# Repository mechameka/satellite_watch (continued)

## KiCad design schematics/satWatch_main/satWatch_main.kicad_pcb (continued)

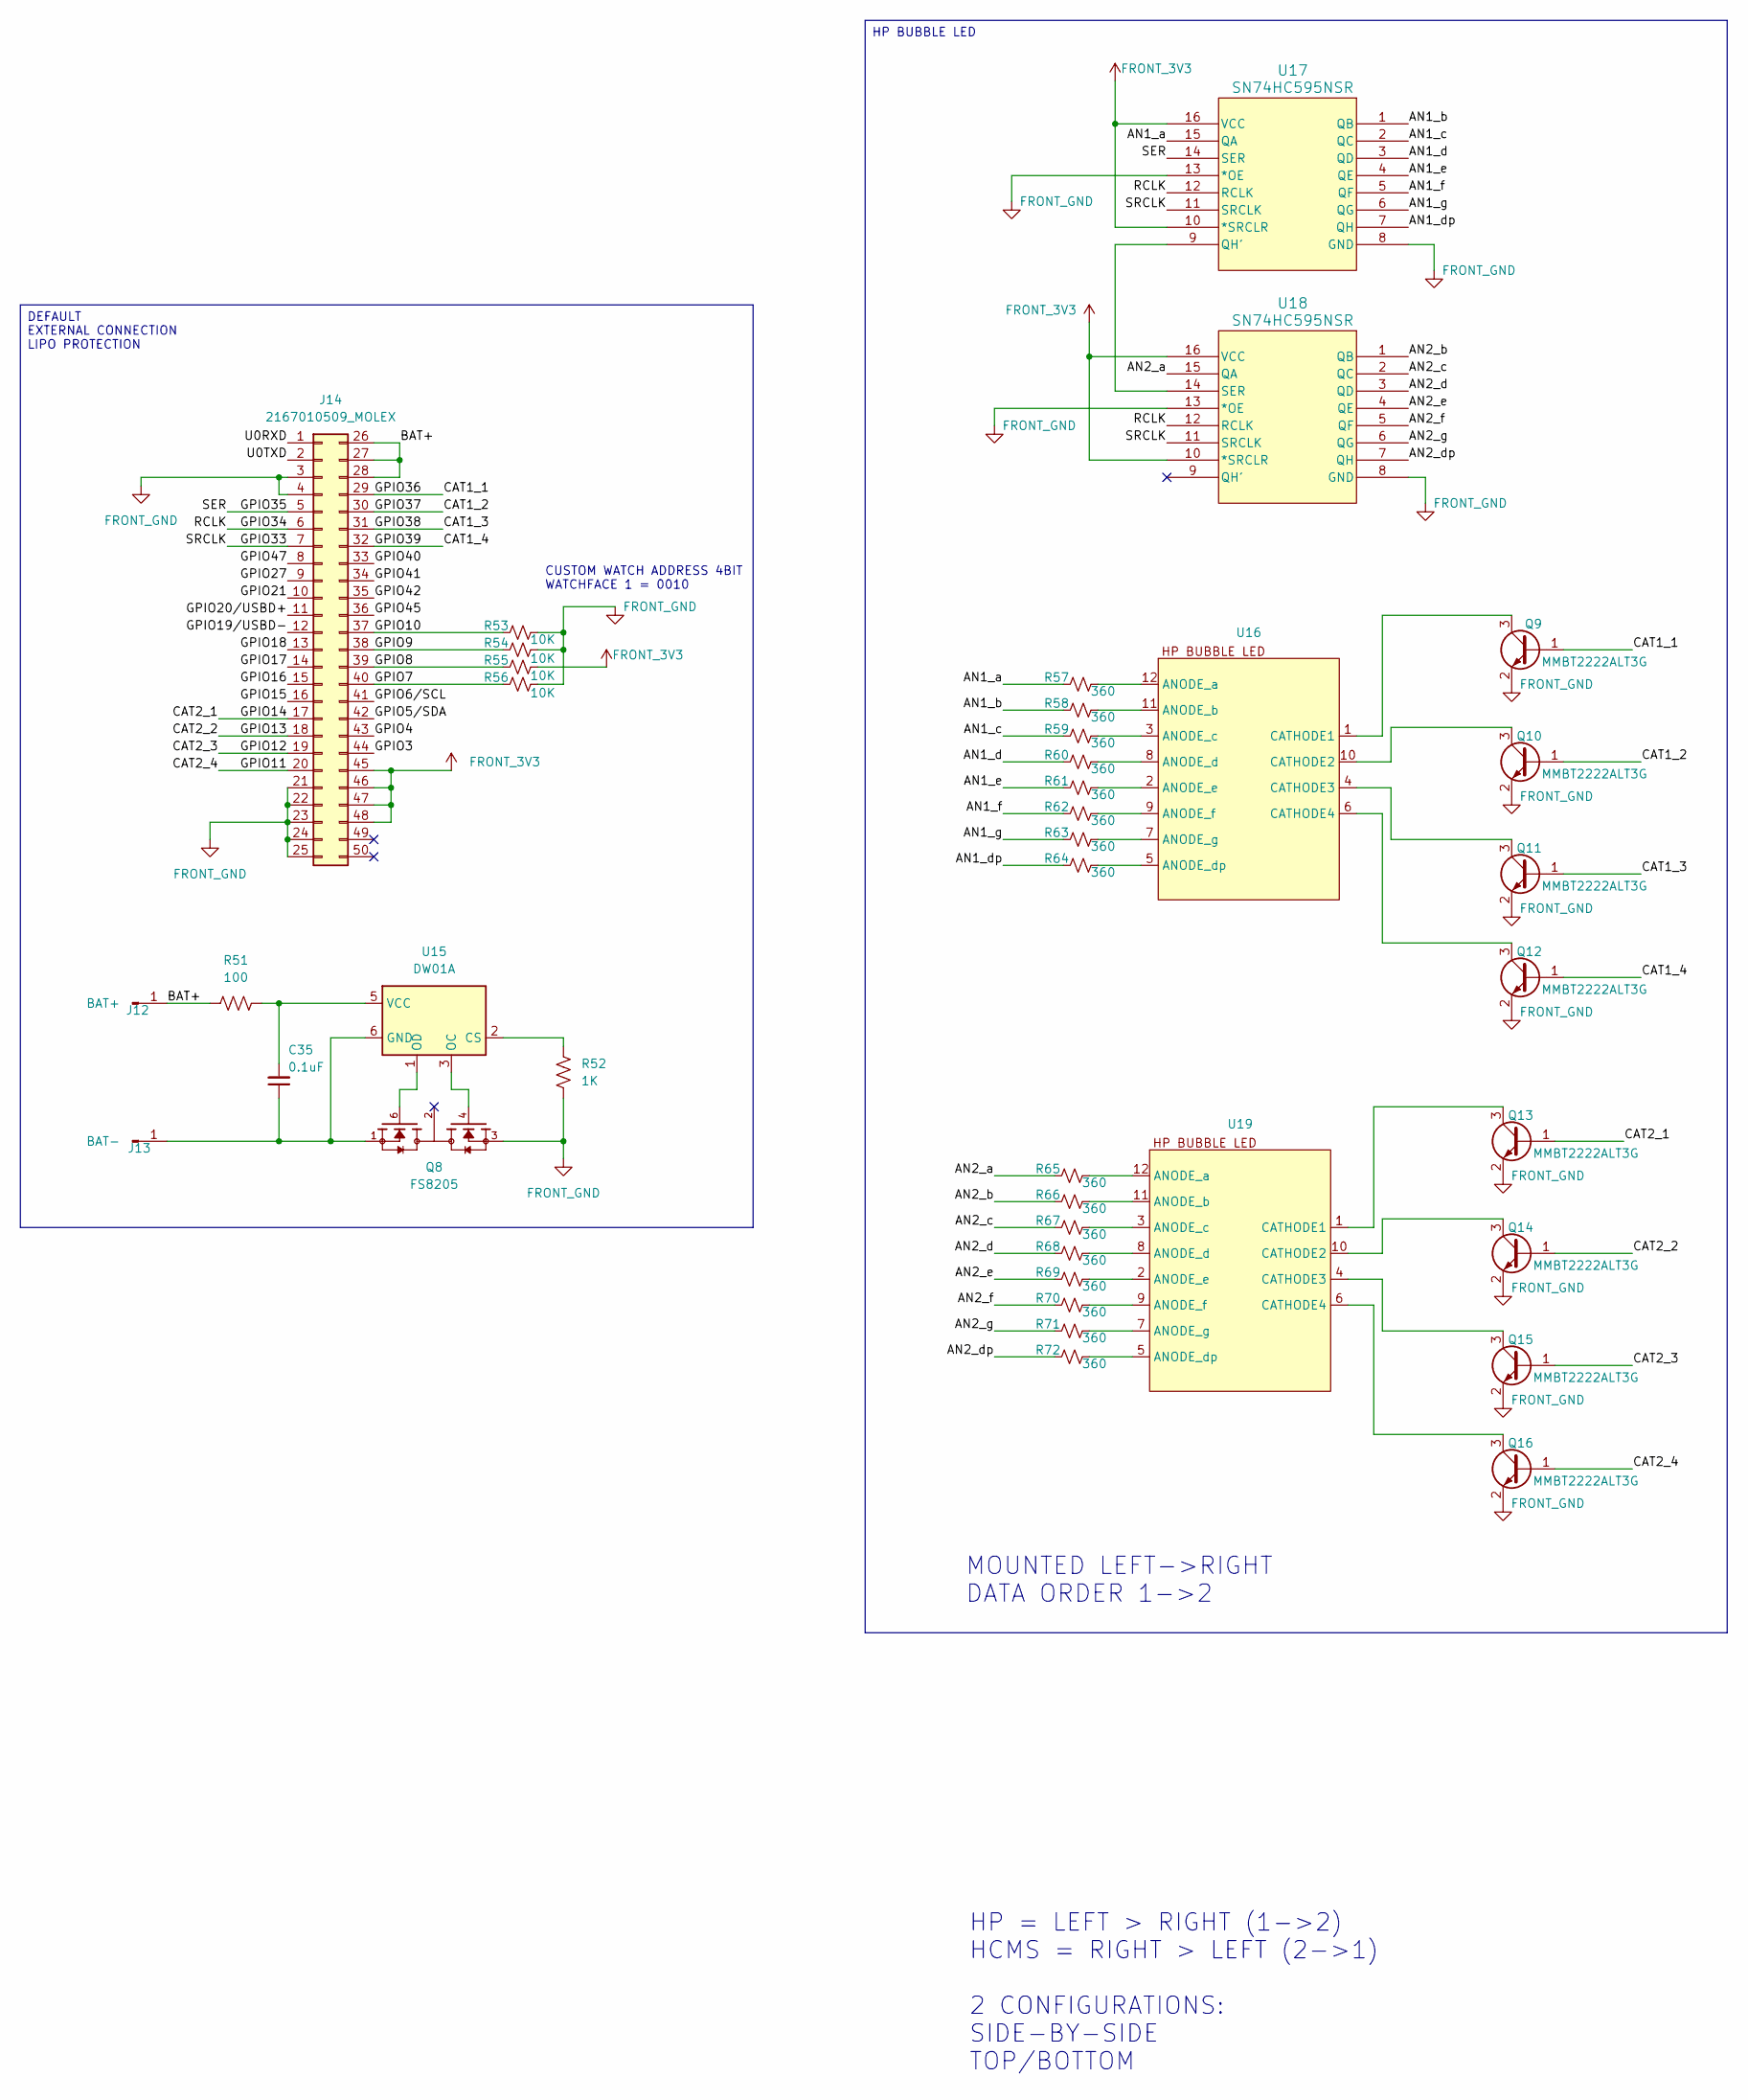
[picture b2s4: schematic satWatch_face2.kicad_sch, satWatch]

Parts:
C35: 0.1uF; C_0402_1005Metric_Pad0.74x0.62mm_HandSolder
J12: BAT+; SolderWirePad_1x01_SMD_3x6mm
J13: BAT-; SolderWirePad_1x01_SMD_3x6mm
J14: 2167010509_MOLEX; CON_2167010509_MOL
Q8: FS8205; SOT95P280X145-6N; PARTREV 1.9
Q9, Q10, Q11, Q12, Q13, Q14, Q15, Q16: MMBT2222ALT3G; SOT-23
R51: 100; R_0402_1005Metric_Pad0.72x0.64mm_HandSolder
R52: 1K; R_0402_1005Metric_Pad0.72x0.64mm_HandSolder
R53, R54, R55, R56: 10K; R_0402_1005Metric_Pad0.72x0.64mm_HandSolder
R57, R58, R59, R60, R61, R62, R63, R64, R65, R66, R67, R68, R69, R70, R71, R72: 360; R_0402_1005Metric_Pad0.72x0.64mm_HandSolder
U15: DW01A; SOT-23-6
U16, U19: DIP-12_W7.62mm
U17, U18: SN74HC595NSR; NS16-L

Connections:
/face2/AN1_a: R57.1, U17.15 (QA)
/face2/AN1_b: R58.1, U17.1 (QB)
/face2/AN1_c: R59.1, U17.2 (QC)
/face2/AN1_d: R60.1, U17.3 (QD)
/face2/AN1_dp: R64.1, U17.7 (QH)
/face2/AN1_e: R61.1, U17.4 (QE)
/face2/AN1_f: R62.1, U17.5 (QF)
/face2/AN1_g: R63.1, U17.6 (QG)
/face2/AN2_a: R65.1, U18.15 (QA)
/face2/AN2_b: R66.1, U18.1 (QB)
/face2/AN2_c: R67.1, U18.2 (QC)
/face2/AN2_d: R68.1, U18.3 (QD)
/face2/AN2_dp: R72.1, U18.7 (QH)
/face2/AN2_e: R69.1, U18.4 (QE)
/face2/AN2_f: R70.1, U18.5 (QF)
/face2/AN2_g: R71.1, U18.6 (QG)
/face2/BAT+: J12.1 (Pin_1_1), J14.26, J14.27, J14.28, R51.1
/face2/CAT1_1: J14.29, Q9.1 (B)
/face2/CAT1_2: J14.30, Q10.1 (B)
/face2/CAT1_3: J14.31, Q11.1 (B)
/face2/CAT1_4: J14.32, Q12.1 (B)
/face2/CAT2_1: J14.17, Q13.1 (B)
/face2/CAT2_2: J14.18, Q14.1 (B)
/face2/CAT2_3: J14.19, Q15.1 (B)
/face2/CAT2_4: J14.20, Q16.1 (B)
/face2/GPIO3: J14.44
/face2/GPIO4: J14.43
/face2/GPIO5/SDA: J14.42
/face2/GPIO6/SCL: J14.41
/face2/GPIO7: J14.40, R56.1
/face2/GPIO8: J14.39, R55.1
/face2/GPIO9: J14.38, R54.1
/face2/GPIO10: J14.37, R53.1
/face2/GPIO15: J14.16
/face2/GPIO16: J14.15
/face2/GPIO17: J14.14
/face2/GPIO18: J14.13
/face2/GPIO19/USBD-: J14.12
/face2/GPIO20/USBD+: J14.11
/face2/GPIO21: J14.10
/face2/GPIO27: J14.9
/face2/GPIO33: J14.7, U17.11 (SRCLK), U18.11 (SRCLK)
/face2/GPIO34: J14.6, U17.12 (RCLK), U18.12 (RCLK)
/face2/GPIO35: J14.5, U17.14 (SER)
/face2/GPIO40: J14.33
/face2/GPIO41: J14.34
/face2/GPIO42: J14.35
/face2/GPIO45: J14.36
/face2/GPIO47: J14.8
/face2/U0RXD: J14.1
/face2/U0TXD: J14.2
FRONT_3V3: J14.45, J14.46, J14.47, J14.48, R55.2, U17.10 (*SRCLR), U17.16 (VCC), U18.10 (*SRCLR), U18.16 (VCC); also elsewhere on the board
FRONT_GND: J14.3, J14.4, J14.21, J14.22, J14.23, J14.24, J14.25, Q8.3, Q9.2 (E), Q10.2 (E), Q11.2 (E), Q12.2 (E), Q13.2 (E), Q14.2 (E), Q15.2 (E), Q16.2 (E), R52.1, R53.2, R54.2, R56.2, U17.8 (GND), U17.13 (*OE), U18.8 (GND), U18.13 (*OE); also elsewhere on the board
unnamed: C35.1, J13.1 (Pin_1_1), Q8.1, U15.6 (GND)
unnamed: Q9.3 (C), U16.1 (CATHODE1)
unnamed: Q10.3 (C), U16.10 (CATHODE2)
unnamed: Q11.3 (C), U16.4 (CATHODE3)
unnamed: Q12.3 (C), U16.6 (CATHODE4)
unnamed: Q13.3 (C), U19.1 (CATHODE1)
unnamed: Q14.3 (C), U19.10 (CATHODE2)
unnamed: Q15.3 (C), U19.4 (CATHODE3)
unnamed: Q16.3 (C), U19.6 (CATHODE4)
unnamed: R52.2, U15.2 (CS)
unnamed: Q8.4, U15.3 (OC)
unnamed: Q8.6, U15.1 (OD)
unnamed: C35.2, R51.2, U15.5 (VCC)
unnamed: R57.2, U16.12 (ANODE_a)
unnamed: R58.2, U16.11 (ANODE_b)
unnamed: R59.2, U16.3 (ANODE_c)
unnamed: R60.2, U16.8 (ANODE_d)
unnamed: R64.2, U16.5 (ANODE_dp)
unnamed: R61.2, U16.2 (ANODE_e)
unnamed: R62.2, U16.9 (ANODE_f)
unnamed: R63.2, U16.7 (ANODE_g)
unnamed: U17.9 (QH'), U18.14 (SER)
unnamed: R65.2, U19.12 (ANODE_a)
unnamed: R66.2, U19.11 (ANODE_b)
unnamed: R67.2, U19.3 (ANODE_c)
unnamed: R68.2, U19.8 (ANODE_d)
unnamed: R72.2, U19.5 (ANODE_dp)
unnamed: R69.2, U19.2 (ANODE_e)
unnamed: R70.2, U19.9 (ANODE_f)
unnamed: R71.2, U19.7 (ANODE_g)

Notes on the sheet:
MOUNTED LEFT->RIGHT DATA ORDER 1->2
CUSTOM WATCH ADDRESS 4BIT WATCHFACE 1 = 0010
HP = LEFT > RIGHT (1->2) HCMS = RIGHT > LEFT (2->1) 2 CONFIGURATIONS: SIDE-BY-SIDE TOP/BOTTOM
DEFAULT EXTERNAL CONNECTION LIPO PROTECTION
HP BUBBLE LED

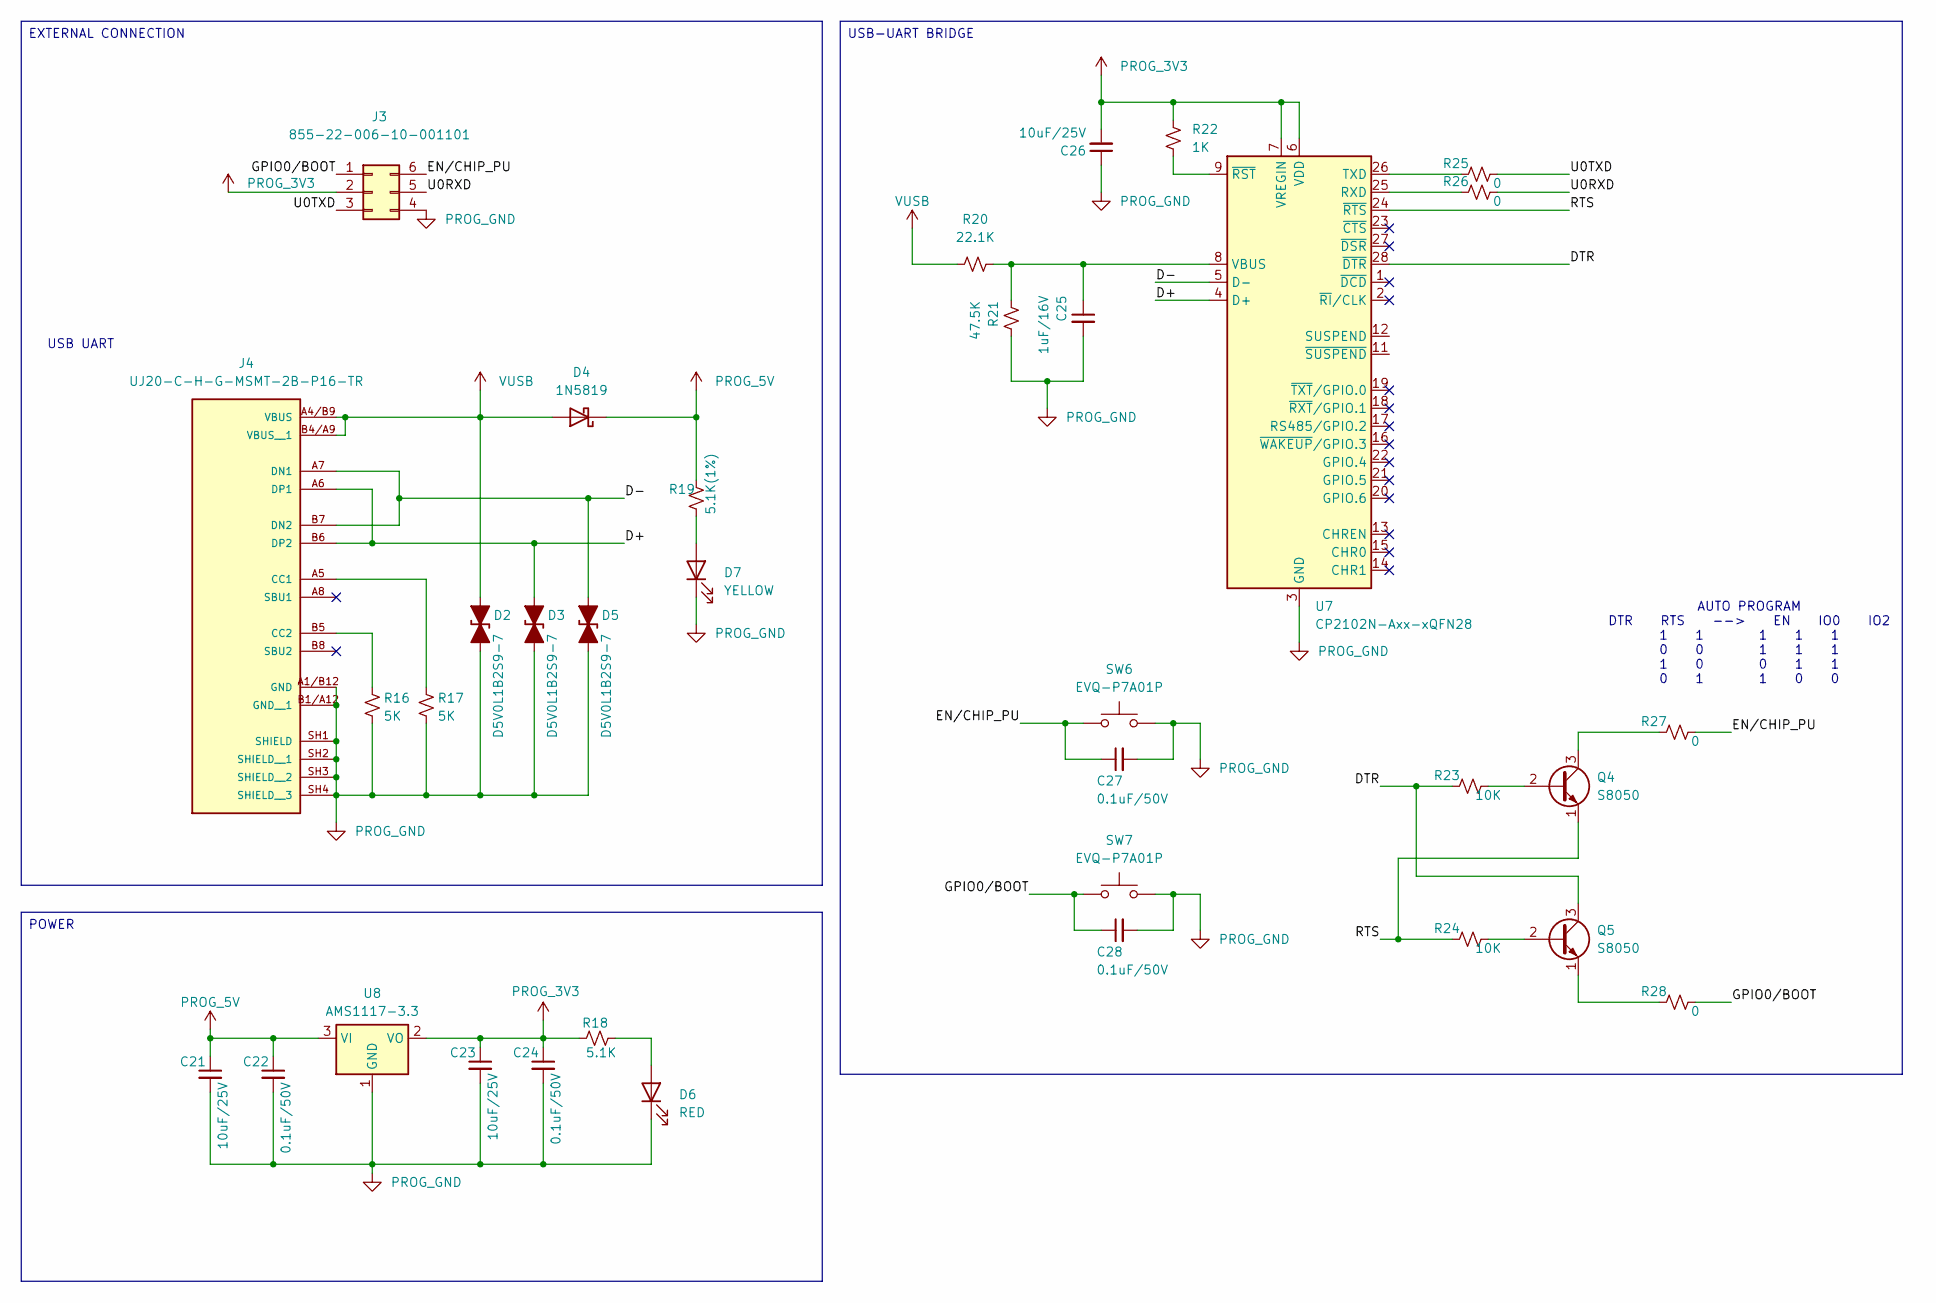
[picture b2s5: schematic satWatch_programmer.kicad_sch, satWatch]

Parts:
C21, C23, C26: 10uF/25V; C_0603_1608Metric_Pad1.08x0.95mm_HandSolder
C22, C24, C27, C28: 0.1uF/50V; C_0603_1608Metric_Pad1.08x0.95mm_HandSolder
C25: 1uF/16V; C_0603_1608Metric_Pad1.08x0.95mm_HandSolder
D2, D3, D5: D5V0L1B2S9-7; D_SOD-923
D4: 1N5819; D_SOD-123
D6: RED; LED_0603_1608Metric_Pad1.05x0.95mm_HandSolder
D7: YELLOW; LED_0603_1608Metric_Pad1.05x0.95mm_HandSolder
J3: 855-22-006-10-001101; 8552200610001101
J4: UJ20-C-H-G-MSMT-2B-P16-TR; SAMESKY_UJ20-C-H-G-MSMT-2B-P16-TR; PARTREV 1.0
Q4, Q5: S8050; SOT-23_Handsoldering
R16, R17: 5K; R_0603_1608Metric_Pad0.98x0.95mm_HandSolder
R18: 5.1K; R_0603_1608Metric_Pad0.98x0.95mm_HandSolder
R19: 5.1K(1%); R_0603_1608Metric_Pad0.98x0.95mm_HandSolder
R20: 22.1K; R_0603_1608Metric_Pad0.98x0.95mm_HandSolder
R21: 47.5K; R_0603_1608Metric_Pad0.98x0.95mm_HandSolder
R22: 1K; R_0603_1608Metric_Pad0.98x0.95mm_HandSolder
R23, R24: 10K; R_0603_1608Metric_Pad0.98x0.95mm_HandSolder
R25, R26, R27, R28: 0; R_0603_1608Metric_Pad0.98x0.95mm_HandSolder
SW6, SW7: EVQ-P7A01P; SW_SPST_EVQP7A
U7: CP2102N-Axx-xQFN28; QFN-28-1EP_5x5mm_P0.5mm_EP3.35x3.35mm
U8: AMS1117-3.3; SOT-223-3_TabPin2

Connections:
/Programmer/D+: D3.1 (A1), J4.A6 (DP1), J4.B6 (DP2), U7.4 (D+)
/Programmer/D-: D5.1 (A1), J4.A7 (DN1), J4.B7 (DN2), U7.5 (D-)
/Programmer/DTR: Q5.3 (C), R23.2, U7.28 (~DTR)
/Programmer/EN/CHIP_PU: C27.1, J3.6, R27.1, SW6.1
/Programmer/GPIO0/BOOT: C28.1, J3.1, R28.1, SW7.1
/Programmer/RTS: Q4.1 (E), R24.2, U7.24 (~RTS)
/Programmer/U0RXD: J3.5, R26.1
/Programmer/U0TXD: J3.3, R25.1
unnamed: D6.2 (A), R18.2
unnamed: D7.2 (A), R19.1
unnamed: J4.A5 (CC1), R17.1
unnamed: J4.B5 (CC2), R16.1
unnamed: Q4.2 (B), R23.1
unnamed: Q4.3 (C), R27.2
unnamed: Q5.2 (B), R24.1
unnamed: Q5.1 (E), R28.2
unnamed: R26.2, U7.25 (RXD)
unnamed: R25.2, U7.26 (TXD)
unnamed: C25.1, R20.2, R21.1, U7.8 (VBUS)
unnamed: R22.1, U7.9 (~RST)
PROG_3V3: C23.1, C24.1, C26.2, J3.2, R18.1, R22.2, U7.6 (VDD), U7.7 (VREGIN), U8.2 (VO)
PROG_5V: C21.1, C22.1, D4.1 (K), R19.2, U8.3 (VI)
PROG_GND: C21.2, C22.2, C23.2, C24.2, C25.2, C26.1, C27.2, C28.2, D2.2 (A2), D3.2 (A2), D5.2 (A2), D6.1 (K), D7.1 (K), J3.4, J4.A1/B12 (GND), J4.B1/A12 (GND__1), J4.SH1 (SHIELD), J4.SH2 (SHIELD__1), J4.SH3 (SHIELD__2), J4.SH4 (SHIELD__3), R16.2, R17.2, R21.2, SW6.2, SW7.2, U7.3 (GND), U7.29 (GND), U8.1 (GND)
VUSB: D2.1 (A1), D4.2 (A), J4.A4/B9 (VBUS), J4.B4/A9 (VBUS__1), R20.1

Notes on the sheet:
USB UART
AUTO PROGRAM DTR RTS --> EN IO0 IO2 1 1 1 1 1 0 0 1 1 1 1 0 0 1 1 0 1 1 0 0
USB-UART BRIDGE
EXTERNAL CONNECTION
POWER

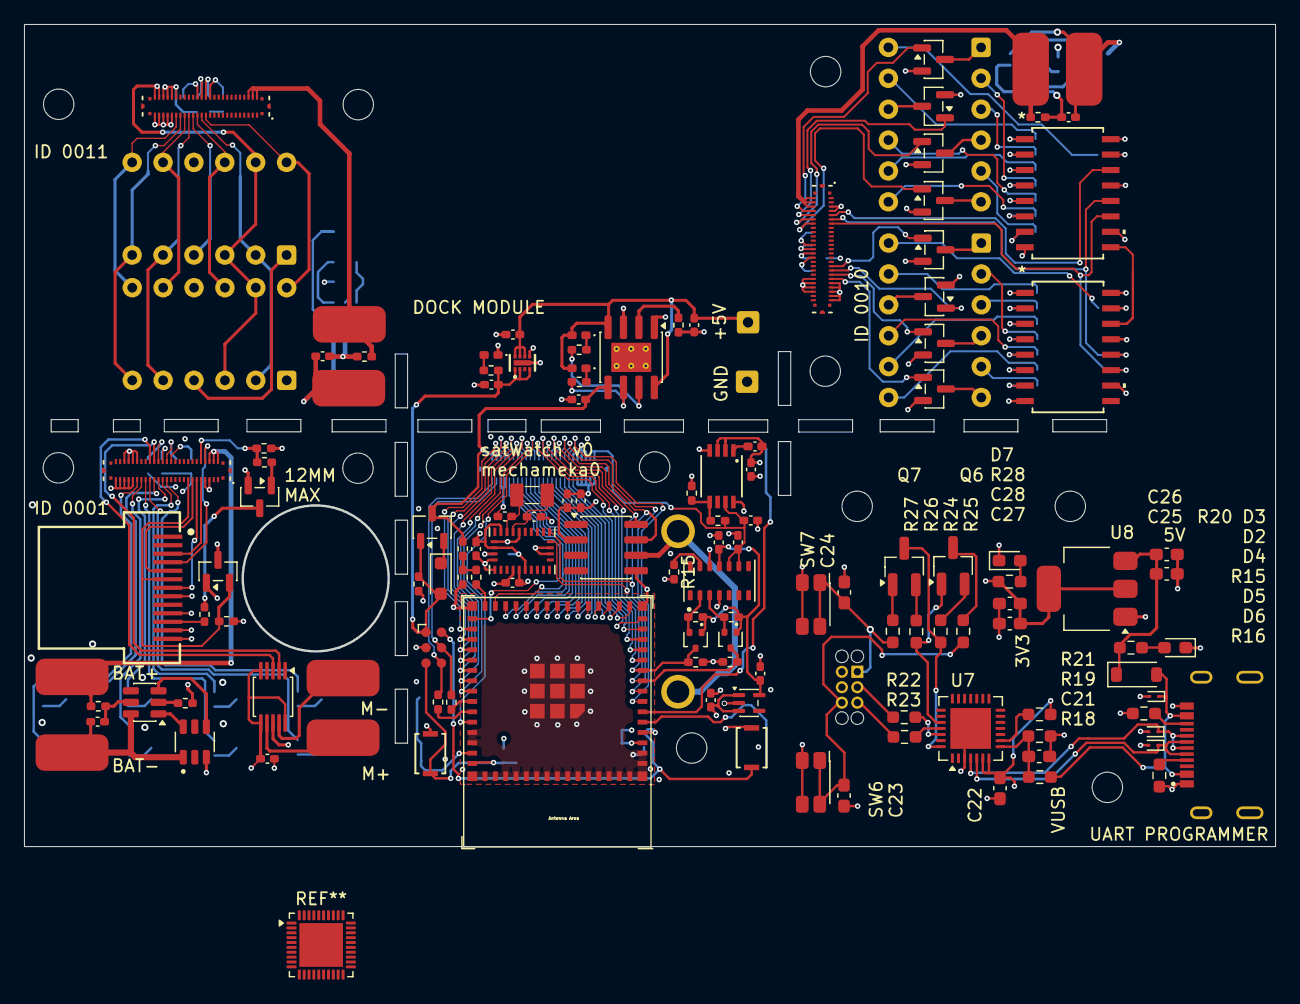
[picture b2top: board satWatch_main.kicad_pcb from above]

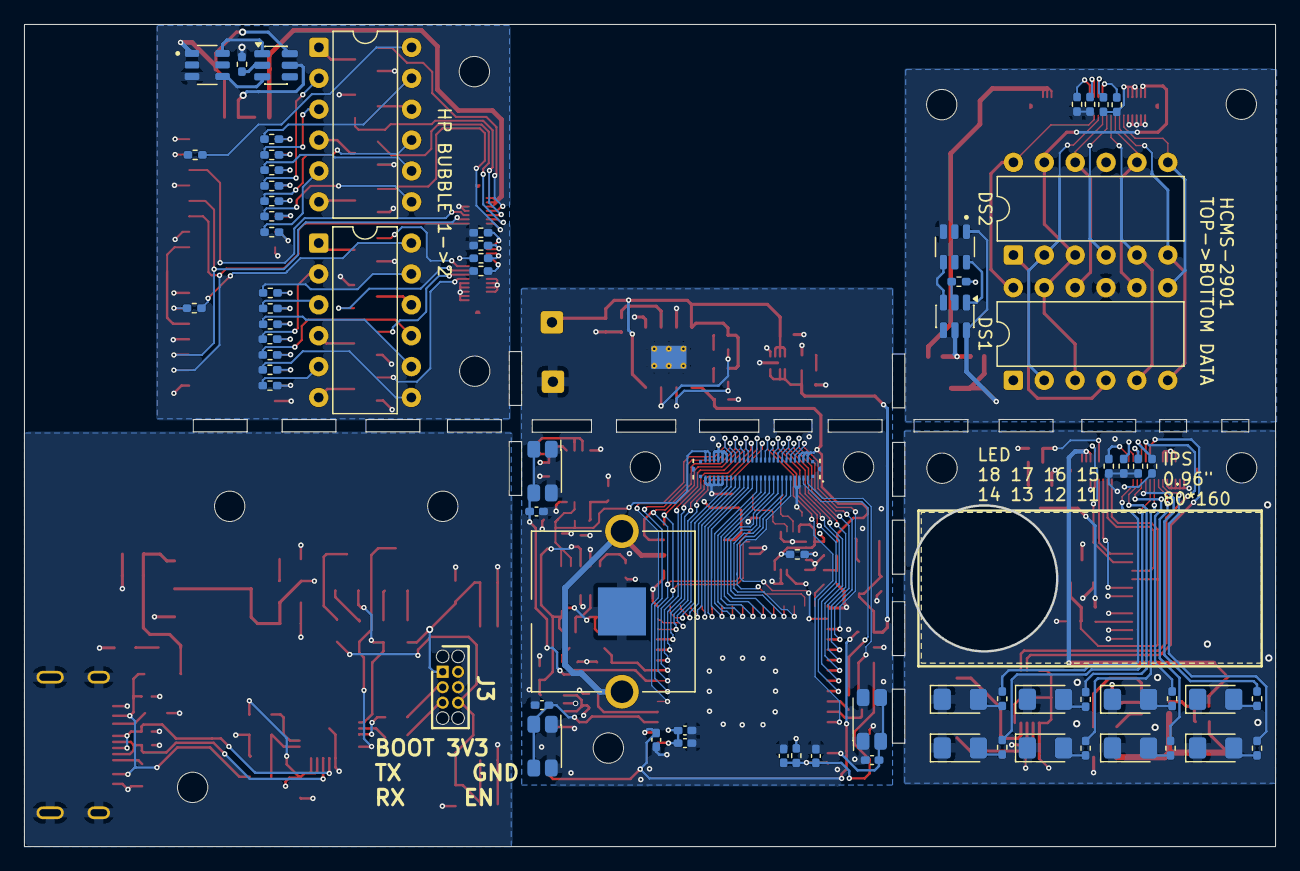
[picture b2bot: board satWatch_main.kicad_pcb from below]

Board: 4 copper layers, 102.9 x 67.6 mm, 210 parts (70 on the bottom side), 213 nets.

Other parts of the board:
H1, H1#2, H1#3, H1#4, H1#5, H2, H2#2, H2#3, H2#4, H2#5, H3, H3#2: MountingHole; MountingHole_2.5mm

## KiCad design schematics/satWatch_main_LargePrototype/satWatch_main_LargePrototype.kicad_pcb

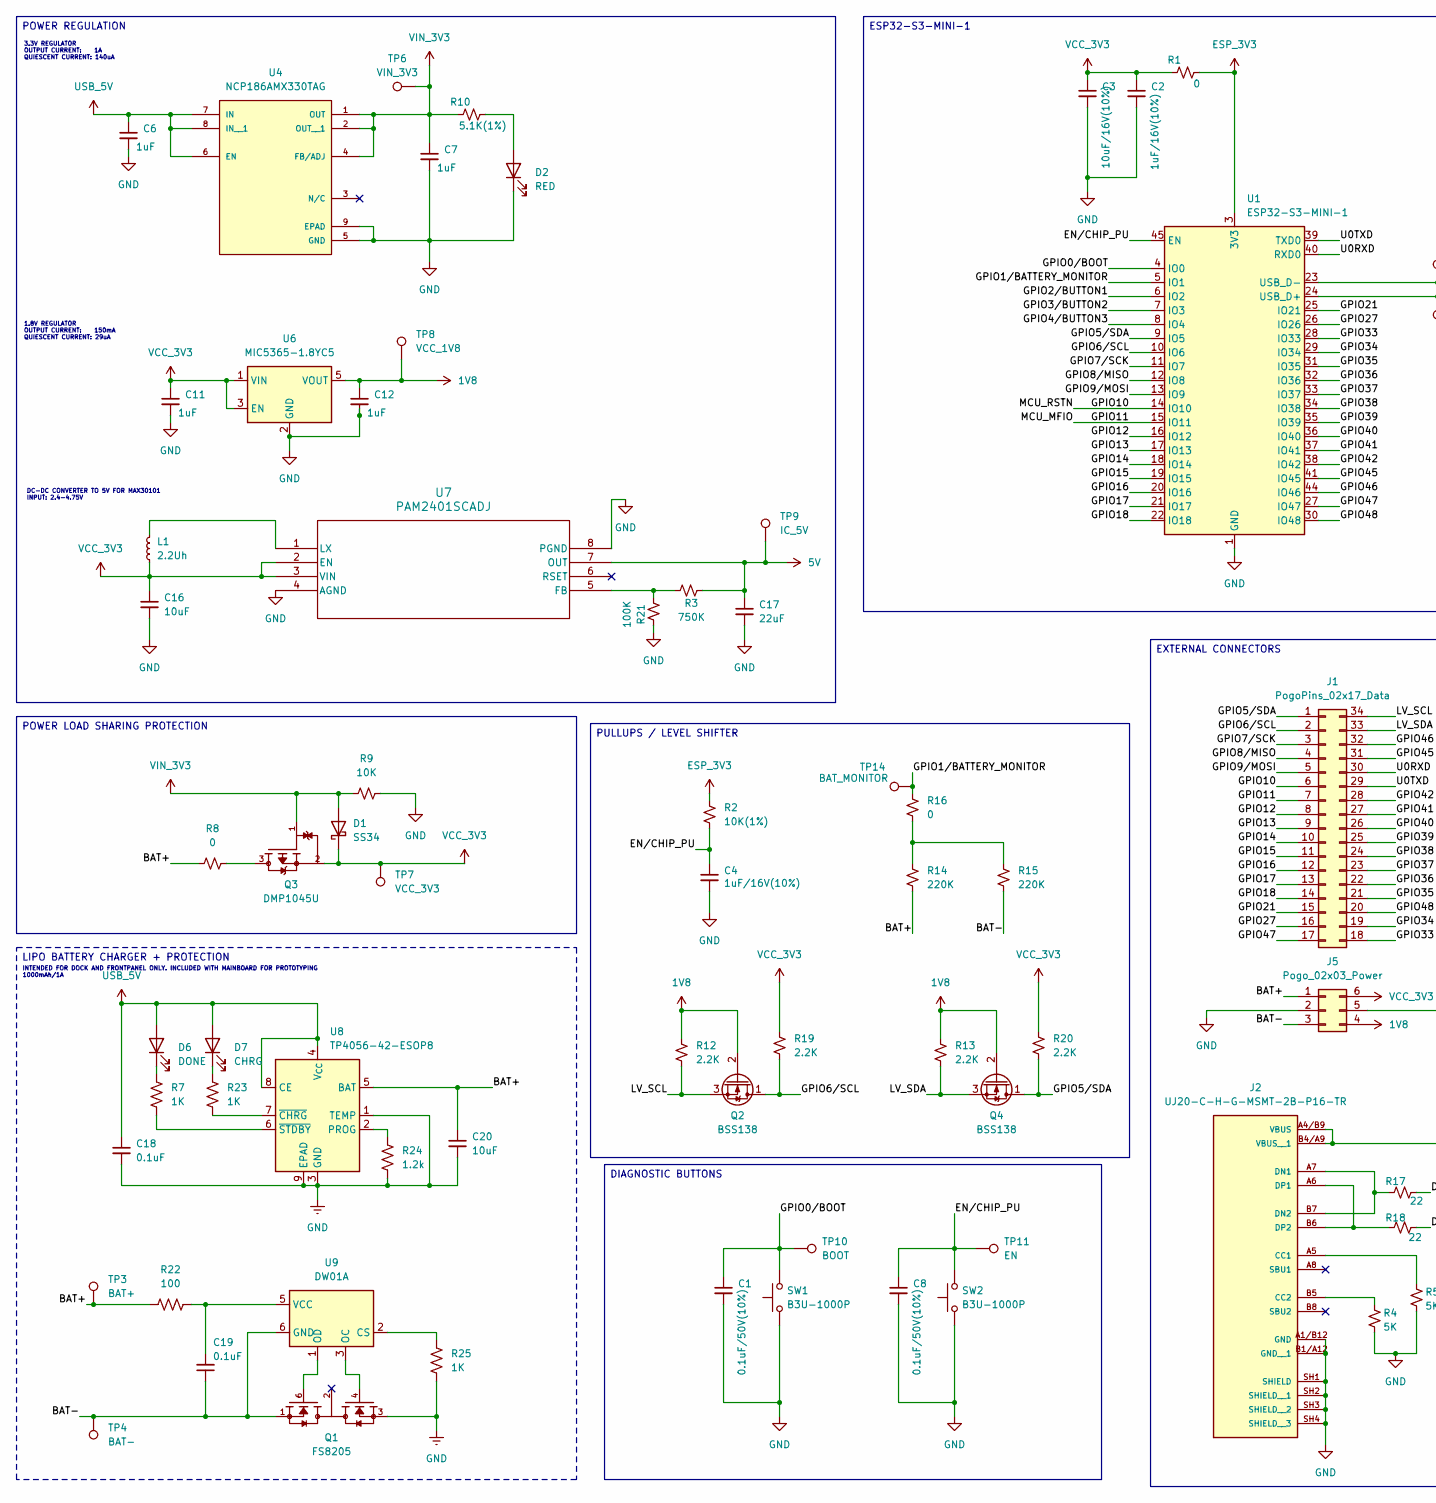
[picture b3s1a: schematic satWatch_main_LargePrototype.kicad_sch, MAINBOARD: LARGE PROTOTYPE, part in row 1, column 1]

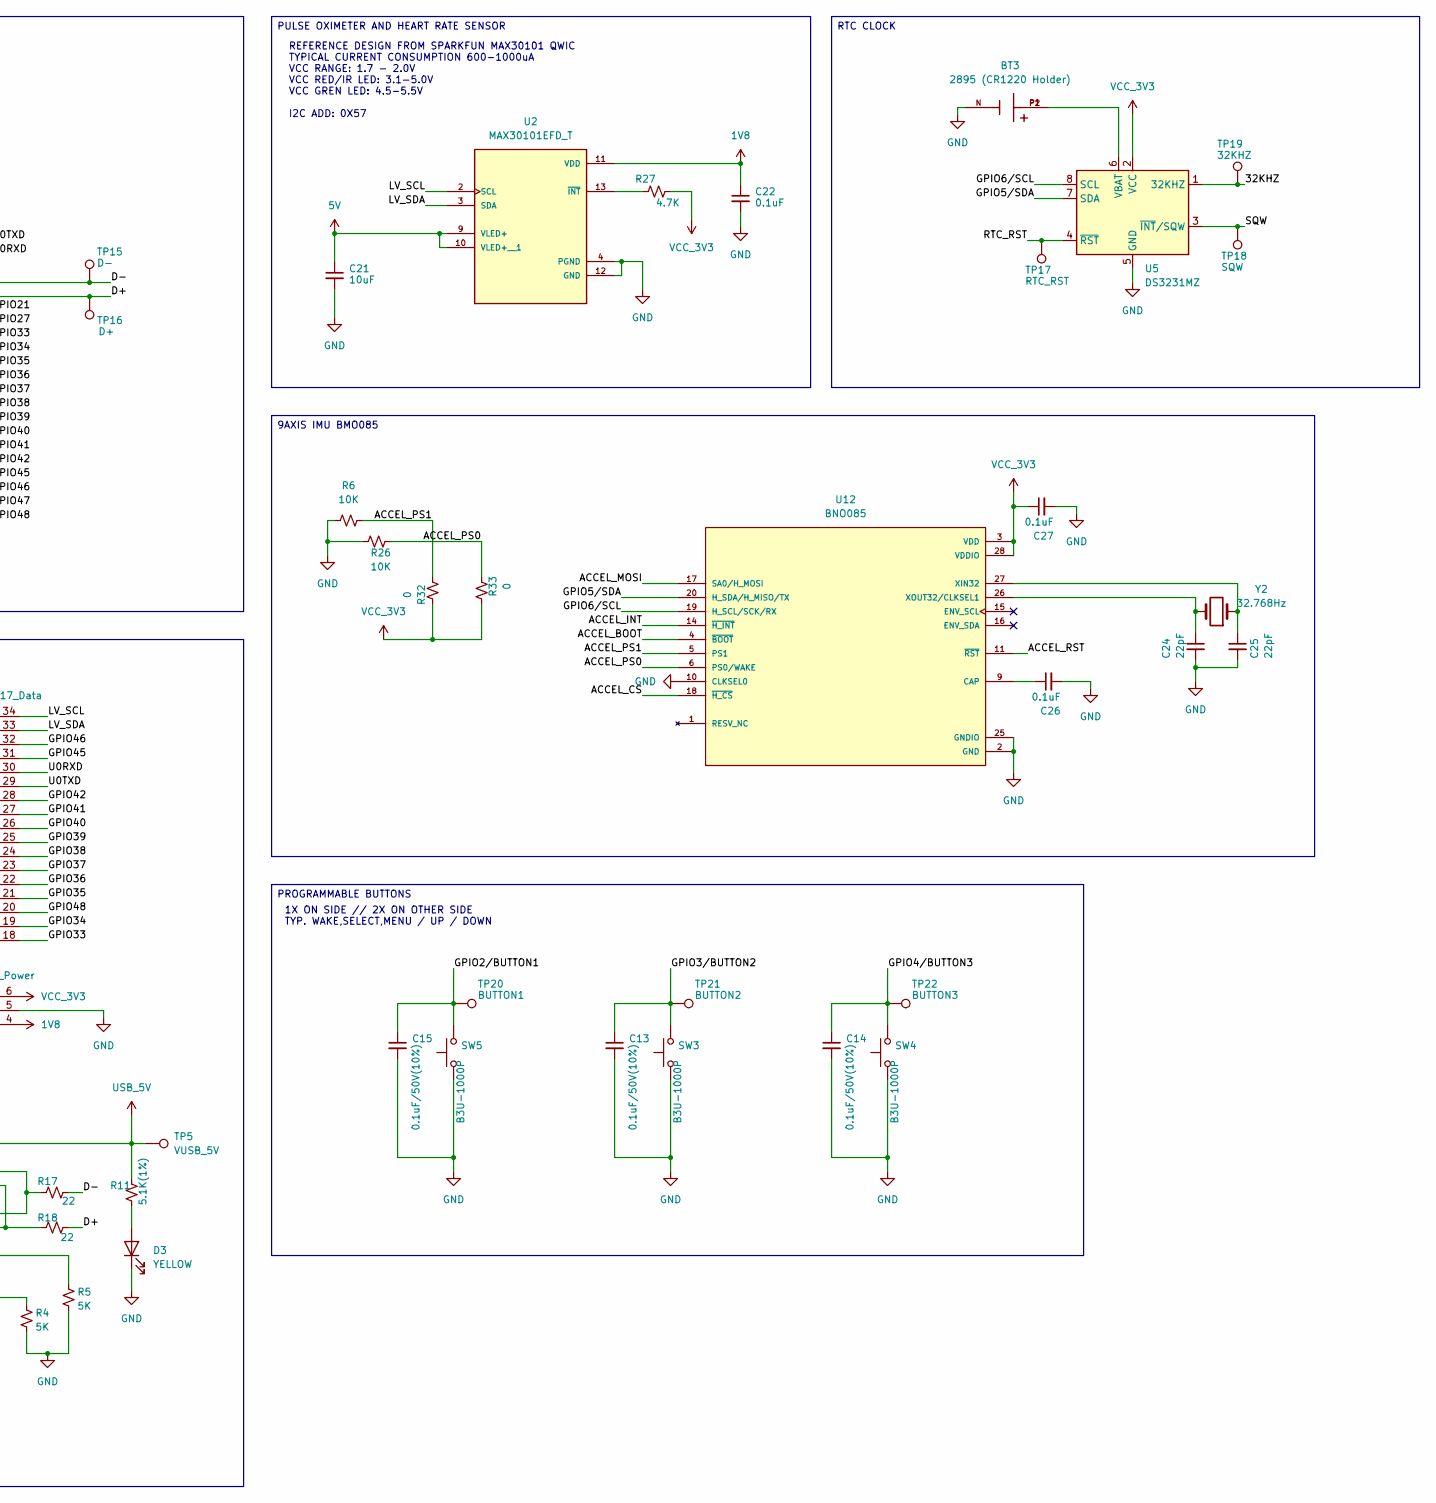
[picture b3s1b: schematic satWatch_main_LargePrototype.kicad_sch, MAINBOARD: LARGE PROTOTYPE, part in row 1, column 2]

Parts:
BT3: 2895 (CR1220 Holder); BAT_2895; PARTREV B
C1, C8, C13, C14, C15: 0.1uF/50V(10%); C_0603_1608Metric_Pad1.08x0.95mm_HandSolder
C2, C4: 1uF/16V(10%); C_0603_1608Metric_Pad1.08x0.95mm_HandSolder
C3: 10uF/16V(10%); C_0603_1608Metric_Pad1.08x0.95mm_HandSolder
C6, C7, C11, C12: 1uF; C_0603_1608Metric_Pad1.08x0.95mm_HandSolder
C16, C20, C21: 10uF; C_0603_1608Metric_Pad1.08x0.95mm_HandSolder
C17: 22uF; C_0603_1608Metric_Pad1.08x0.95mm_HandSolder
C18, C19, C22, C26, C27: 0.1uF; C_0603_1608Metric_Pad1.08x0.95mm_HandSolder
C24, C25: 22pF; C_0603_1608Metric_Pad1.08x0.95mm_HandSolder
D1: SS34; D_0603_1608Metric_Pad1.05x0.95mm_HandSolder
D2: RED; LED_0603_1608Metric_Pad1.05x0.95mm_HandSolder
D3: YELLOW; LED_0603_1608Metric_Pad1.05x0.95mm_HandSolder
D6: DONE; LED_0603_1608Metric_Pad1.05x0.95mm_HandSolder
D7: CHRG; LED_0603_1608Metric_Pad1.05x0.95mm_HandSolder
J1: PogoPins_02x17_Data; PinHeader_2x17_P2.54mm_Vertical
J2: UJ20-C-H-G-MSMT-2B-P16-TR; SAMESKY_UJ20-C-H-G-MSMT-2B-P16-TR; PARTREV 1.0
J5: Pogo_02x03_Power; PinHeader_2x03_P2.54mm_Vertical
L1: 2.2Uh; L_0603_1608Metric_Pad1.05x0.95mm_HandSolder
Q1: FS8205; SOT95P280X145-6N; PARTREV 1.9
Q2, Q4: BSS138; SOT-23-3
Q3: DMP1045U; SOT-23-3; PARTREV 7 - 2
R1, R8, R16, R32, R33: 0; R_0603_1608Metric_Pad0.98x0.95mm_HandSolder
R2: 10K(1%); R_0603_1608Metric_Pad0.98x0.95mm_HandSolder
R3: 750K; R_0603_1608Metric_Pad0.98x0.95mm_HandSolder
R4, R5: 5K; R_0603_1608Metric_Pad0.98x0.95mm_HandSolder
R6, R9, R26: 10K; R_0603_1608Metric_Pad0.98x0.95mm_HandSolder
R7, R23, R25: 1K; R_0603_1608Metric_Pad0.98x0.95mm_HandSolder
R10, R11: 5.1K(1%); R_0603_1608Metric_Pad0.98x0.95mm_HandSolder
R12, R13, R19, R20: 2.2K; R_0603_1608Metric_Pad0.98x0.95mm_HandSolder
R14, R15: 220K; R_0603_1608Metric_Pad0.98x0.95mm_HandSolder
R17, R18: 22; R_0603_1608Metric_Pad0.98x0.95mm_HandSolder
R21: 100K; R_0603_1608Metric_Pad0.98x0.95mm_HandSolder
R22: 100; R_0603_1608Metric_Pad0.98x0.95mm_HandSolder
R24: 1.2k; R_0603_1608Metric_Pad0.98x0.95mm_HandSolder
R27: 4.7K; R_0603_1608Metric_Pad0.98x0.95mm_HandSolder
SW1, SW2, SW3, SW4, SW5: B3U-1000P; SW_SPST_B3U-1000P
TP3: BAT+; TestPoint_Pad_D2.5mm
TP4: BAT-; TestPoint_Pad_D2.5mm
TP5: VUSB_5V; TestPoint_Pad_D2.5mm
TP6: VIN_3V3; TestPoint_Pad_D2.5mm
TP7: VCC_3V3; TestPoint_Pad_D2.5mm
TP8: VCC_1V8; TestPoint_Pad_D2.5mm
TP9: IC_5V; TestPoint_Pad_D2.5mm
TP10: BOOT; TestPoint_Pad_D2.5mm
TP11: EN; TestPoint_Pad_D2.5mm
TP14: BAT_MONITOR; TestPoint_Pad_D2.5mm
TP15: D-; TestPoint_Pad_D2.5mm
TP16: D+; TestPoint_Pad_D2.5mm
TP17: RTC_RST; TestPoint_Pad_D2.5mm
TP18: SQW; TestPoint_Pad_D2.5mm
TP19: 32KHZ; TestPoint_Pad_D2.5mm
TP20: BUTTON1; TestPoint_Pad_D2.5mm
TP21: BUTTON2; TestPoint_Pad_D2.5mm
TP22: BUTTON3; TestPoint_Pad_D2.5mm
U1: ESP32-S3-MINI-1; ESP32-S2-MINI-1
U2: MAX30101EFD_T; MAX30101EFD+T; PARTREV 2
U4: NCP186AMX330TAG; PSON40P160X120X45-9N; PARTREV Rev.5
U5: DS3231MZ; SOIC-8_3.9x4.9mm_P1.27mm
U6: MIC5365-1.8YC5; SOT-353_SC-70-5
U7: PAM2401SCADJ; MSOP8_DIO
U8: TP4056-42-ESOP8; SOIC-8-1EP_3.9x4.9mm_P1.27mm_EP2.41x3.3mm_ThermalVias
U9: DW01A; SOT-23-6
U12: BNO085; IC_BNO085; PARTREV v1.17
Y2: 32.768Hz; ABS07-32.768KHZ-T

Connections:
1V8: C12.1, C22.1, J5.4, Q2.2 (G), Q4.2 (G), R12.1, R13.1, TP8.1 (1_1), U2.11 (VDD), U6.5 (VOUT)
5V: C17.1, C21.1, R3.2, TP9.1 (1_1), U2.9 (VLED+), U2.10 (VLED+__1), U7.7 (OUT)
/32KHZ: TP19.1 (1_1), U5.1 (32KHZ)
/ACCEL_BOOT: U12.4 (~BOOT)
/ACCEL_CS: U12.18 (~H_CS)
/ACCEL_INT: U12.14 (~H_INT)
/ACCEL_MOSI: U12.17 (SA0/H_MOSI)
/ACCEL_PS0: R26.2, R33.2, U12.6 (PS0/WAKE)
/ACCEL_PS1: R6.2, R32.1, U12.5 (PS1)
/ACCEL_RST: U12.11 (~RST)
/BAT+: C20.1, J5.1, R8.1, R14.2, R22.1, TP3.1 (1_1), U8.5 (BAT)
/BAT-: C19.1, J5.3, Q1.1, R15.2, TP4.1 (1_1), U9.6 (GND)
/D+: R18.1, TP16.1 (1_1), U1.24 (USB_D+)
/D-: R17.1, TP15.1 (1_1), U1.23 (USB_D-)
/EN/CHIP_PU: C4.1, C8.1, R2.2, SW2.2, TP11.1 (1_1), U1.45 (EN)
/GPIO0/BOOT: C1.1, SW1.2, TP10.1 (1_1), U1.4 (IO0)
/GPIO1/BATTERY_MONITOR: R16.1, TP14.1 (1_1), U1.5 (IO1)
/GPIO2/BUTTON1: C15.1, SW5.2, TP20.1 (1_1), U1.6 (IO2)
/GPIO3/BUTTON2: C13.1, SW3.2, TP21.1 (1_1), U1.7 (IO3)
/GPIO4/BUTTON3: C14.1, SW4.2, TP22.1 (1_1), U1.8 (IO4)
/GPIO5/SDA: J1.1, Q4.1 (D), R20.2, U1.9 (IO5), U5.7 (SDA), U12.20 (H_SDA/H_MISO/TX)
/GPIO6/SCL: J1.2, Q2.1 (D), R19.2, U1.10 (IO6), U5.8 (SCL), U12.19 (H_SCL/SCK/RX)
/GPIO7/SCK: J1.3, U1.11 (IO7)
/GPIO8/MISO: J1.4, U1.12 (IO8)
/GPIO9/MOSI: J1.5, U1.13 (IO9)
/GPIO10: J1.6, U1.14 (IO10)
/GPIO11: J1.7, U1.15 (IO11)
/GPIO12: J1.8, U1.16 (IO12)
/GPIO13: J1.9, U1.17 (IO13)
/GPIO14: J1.10, U1.18 (IO14)
/GPIO15: J1.11, U1.19 (IO15)
/GPIO16: J1.12, U1.20 (IO16)
/GPIO17: J1.13, U1.21 (IO17)
/GPIO18: J1.14, U1.22 (IO18)
/GPIO21: J1.15, U1.25 (IO21)
/GPIO27: J1.16, U1.26 (IO26)
/GPIO33: J1.18, U1.28 (IO33)
/GPIO34: J1.19, U1.29 (IO34)
/GPIO35: J1.21, U1.31 (IO35)
/GPIO36: J1.22, U1.32 (IO36)
/GPIO37: J1.23, U1.33 (IO37)
/GPIO38: J1.24, U1.34 (IO38)
/GPIO39: J1.25, U1.35 (IO39)
/GPIO40: J1.26, U1.36 (IO40)
/GPIO41: J1.27, U1.37 (IO41)
/GPIO42: J1.28, U1.38 (IO42)
/GPIO45: J1.31, U1.41 (IO45)
/GPIO46: J1.32, U1.44 (IO46)
/GPIO47: J1.17, U1.27 (IO47)
/GPIO48: J1.20, U1.30 (IO48)
/LV_SCL: J1.34, Q2.3 (S), R12.2, U2.2 (SCL)
/LV_SDA: J1.33, Q4.3 (S), R13.2, U2.3 (SDA)
/RTC_RST: TP17.1 (1_1), U5.4 (~RST)
/SQW: TP18.1 (1_1), U5.3 (~INT/SQW)
/U0RXD: J1.30, U1.40 (RXD0)
/U0TXD: J1.29, U1.39 (TXD0)
ESP_3V3: R1.2, R2.1, U1.3 (3V3)
GND: BT3.N, C1.2, C2.2, C3.2, C4.2, C6.2, C7.2, C8.2, C11.2, C12.2, C13.2, C14.2, C15.2, C16.2, C17.2, C18.2, C20.2, C21.2, C22.2, C24.2, C25.2, C26.2, C27.2, D2.1 (K), D3.1 (K), J2.A1/B12 (GND), J2.B1/A12 (GND__1), J2.SH1 (SHIELD), J2.SH2 (SHIELD__1), J2.SH3 (SHIELD__2), J2.SH4 (SHIELD__3), J5.2, J5.5, Q1.3, R4.2, R5.2, R6.1, R9.2, R21.2, R24.2, R25.1, R26.1, SW1.1, SW2.1, SW3.1, SW4.1, SW5.1, U1.1 (GND), U1.2 (GND), U1.42 (GND), U1.43 (GND), U1.46 (GND), U1.47 (GND), U1.48 (GND), U1.49 (GND), U1.50 (GND), U1.51 (GND), U1.52 (GND), U1.53 (GND), U1.54 (GND), U1.55 (GND), U1.56 (GND), U1.57 (GND), U1.58 (GND), U1.59 (GND), U1.60 (GND), U1.61 (GND), U1.62 (GND), U1.63 (GND), U1.64 (GND), U1.65 (GND), U2.4 (PGND), U2.12 (GND), U4.5 (GND), U4.9 (EPAD), U5.5 (GND), U6.2 (GND), U7.4 (AGND), U7.8 (PGND), U8.1 (TEMP), U8.3 (GND), U8.9 (EPAD), U12.2 (GND), U12.10 (CLKSEL0), U12.25 (GNDIO)
unnamed: D2.2 (A), R10.2
unnamed: D3.2 (A), R11.1
unnamed: D6.1 (K), R7.1
unnamed: D7.1 (K), R23.1
unnamed: J2.A5 (CC1), R5.1
unnamed: J2.B5 (CC2), R4.1
unnamed: J2.A7 (DN1), J2.B7 (DN2), R17.2
unnamed: J2.A6 (DP1), J2.B6 (DP2), R18.2
unnamed: Q3.3, R8.2
unnamed: R14.1, R15.1, R16.2
unnamed: R27.1, U2.13 (~INT)
unnamed: BT3.P1, BT3.P2, U5.6 (VBAT)
unnamed: R3.1, R21.1, U7.5 (FB)
unnamed: L1.2, U7.1 (LX)
unnamed: R24.1, U8.2 (PROG)
unnamed: R23.2, U8.7 (~CHRG)
unnamed: R7.2, U8.6 (~STDBY)
unnamed: R25.2, U9.2 (CS)
unnamed: Q1.4, U9.3 (OC)
unnamed: Q1.6, U9.1 (OD)
unnamed: C19.2, R22.2, U9.5 (VCC)
unnamed: C26.1, U12.9 (CAP)
unnamed: C25.1, U12.27 (XIN32), Y2.1
unnamed: C24.1, U12.26 (XOUT32/CLKSEL1), Y2.2
USB_5V: C6.1, C18.1, D6.2 (A), D7.2 (A), J2.A4/B9 (VBUS), J2.B4/A9 (VBUS__1), R11.2, TP5.1 (1_1), U4.6 (EN), U4.7 (IN), U4.8 (IN__1), U8.4 (V_{CC}), U8.8 (CE)
VCC_3V3: C2.1, C3.1, C11.1, C16.1, C27.1, D1.1 (K), J5.6, L1.1, Q3.2, R1.1, R19.1, R20.1, R27.2, R32.2, R33.1, TP7.1 (1_1), U5.2 (VCC), U6.1 (VIN), U6.3 (EN), U7.2 (EN), U7.3 (VIN), U12.3 (VDD), U12.28 (VDDIO)
VIN_3V3: C7.1, D1.2 (A), Q3.1, R9.1, R10.1, TP6.1 (1_1), U4.1 (OUT), U4.2 (OUT__1), U4.4 (FB/ADJ)

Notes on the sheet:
INTENDED FOR DOCK AND FRONTPANEL ONLY. INCLUDED WITH MAINBOARD FOR PROTOTYPING 1000mAh/1A
REFERENCE DESIGN FROM SPARKFUN MAX30101 QWIC TYPICAL CURRENT CONSUMPTION 600-1000uA VCC RANGE: 1.7 - 2.0V VCC RED/IR LED: 3.1-5.0V VCC GREN LED: 4.5-5.5V I2C ADD: 0X57
DC-DC CONVERTER TO 5V FOR MAX30101 INPUT: 2.4-4.75V
1.8V REGULATOR OUTPUT CURRENT: 150mA QUIESCENT CURRENT: 29uA
1X ON SIDE // 2X ON OTHER SIDE TYP. WAKE,SELECT,MENU / UP / DOWN
3.3V REGULATOR OUTPUT CURRENT: 1A QUIESCENT CURRENT: 140uA
RTC CLOCK
LIPO BATTERY CHARGER + PROTECTION
POWER REGULATION
ESP32-S3-MINI-1
EXTERNAL CONNECTORS
PULLUPS / LEVEL SHIFTER
9AXIS IMU BMO085
DIAGNOSTIC BUTTONS
PROGRAMMABLE BUTTONS
POWER LOAD SHARING PROTECTION
PULSE OXIMETER AND HEART RATE SENSOR

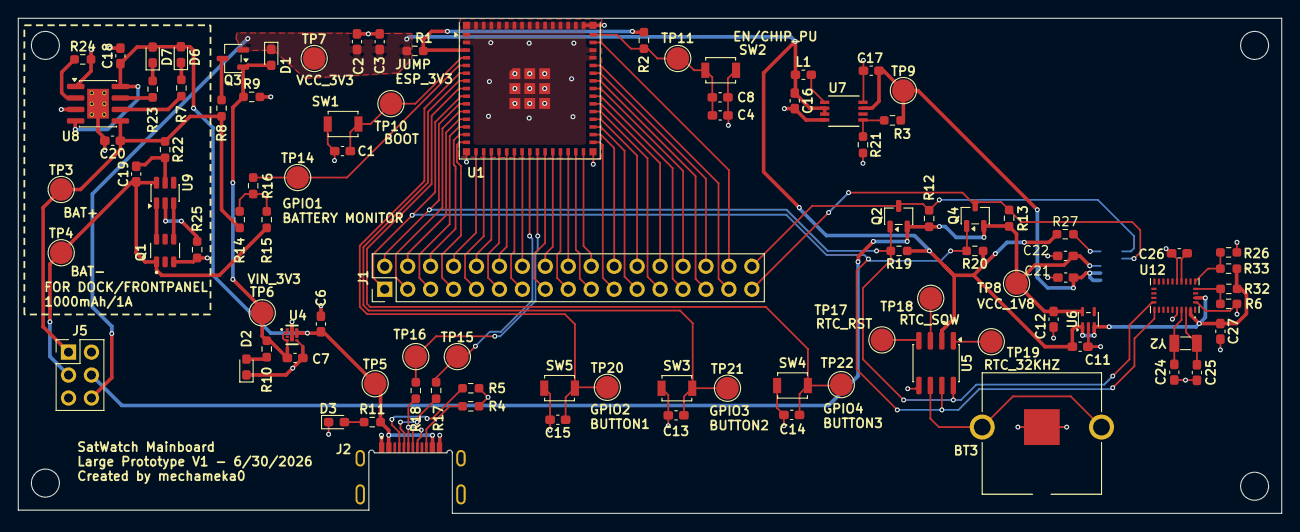
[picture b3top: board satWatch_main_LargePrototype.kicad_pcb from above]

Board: 2 copper layers, 139.8 x 54.8 mm, 99 parts (1 on the bottom side), 80 nets.

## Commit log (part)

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2026-06-10 v0.1
    Initial schematic layout completed
2026-06-10 v0.15
    wip of large-size PCB
2026-06-17 v0.2
    schematic update. prepared file organization for multiple pcb layouts
2026-06-24 v0.3
    Finalized initial draft of large mainboard PCB, ready for first production and testing
2026-06-28 v0.4
    Finalized large prototyping PCB for manufacturing
